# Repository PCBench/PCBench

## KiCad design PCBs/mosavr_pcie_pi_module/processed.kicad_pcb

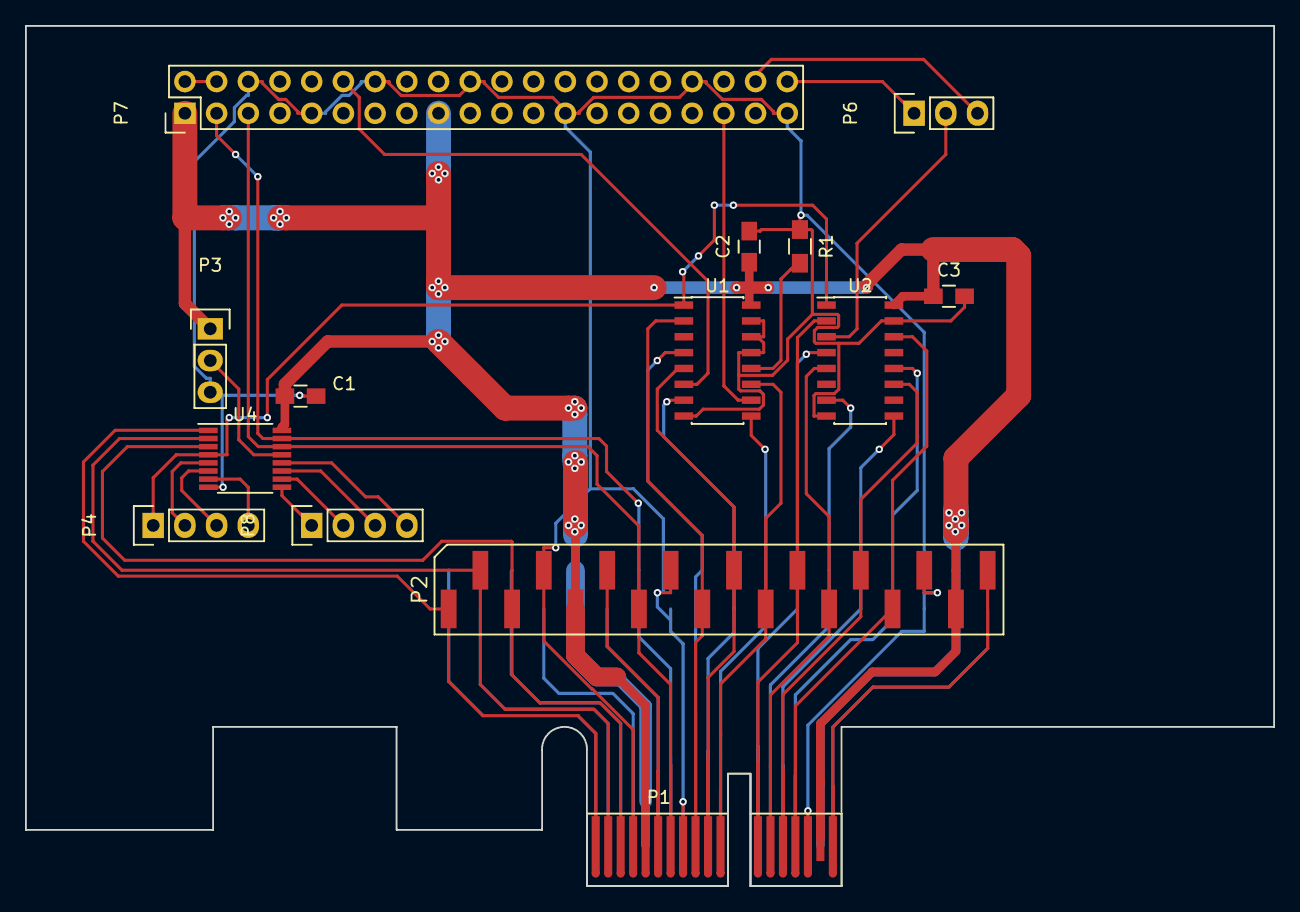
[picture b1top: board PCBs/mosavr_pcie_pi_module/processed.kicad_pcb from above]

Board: 2 copper layers, 100.0 x 68.9 mm, 15 parts (1 on the bottom side), 45 nets.

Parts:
C1, C2, C3: 0.1uF; C_0805_HandSoldering
P1: pcie_1x_edge; PCI-EXPRESS
P2, P5: CONN_01X18; smd_1x18_B
P3, P6: CONN_01X03; Pin_Header_Straight_1x03
P4, P8: CONN_01X04; Pin_Header_Straight_1x04
P7: CONN_02X20; Pin_Header_Straight_2x20
R1: 10k; R_0805_HandSoldering
U1, U2: 74HCT157; SOIC-16_3.9x9.9mm_Pitch1.27mm
U4: PCA9500; TSSOP-16_4.4x5mm_Pitch0.65mm

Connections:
+3V3: C1.1, C2.1, C3.1, P1.A5, P1.A17, P1.B5, P1.B17, P2.5, P2.17, P3.1, P5.5, P5.17, P7.1, P7.17, U1.16, U2.16, U4.16
+5V: P7.2, P7.4
/A0: P1.B1, P2.1, U4.1
/A1: P1.B2, P2.2, U4.2
/A2: P1.B3, P2.3, U4.3
/I2S0_in: P1.B12, P2.12, U2.2
/I2S0_mod: P6.2, U2.3
/I2S0_out: P1.A12, P5.12, U2.4
/I2S1_in: P1.B13, P2.13, U2.5
/I2S1_out: P1.A13, P5.13, U2.7
/I2S2_in: P1.B14, P2.14, U2.11
/I2S2_out: P1.A14, P5.14, U2.9
/I2S3_in: P1.B15, P2.15, U2.14
/I2S3_out: P1.A15, P5.15, U2.12
/LRclk_in: P1.B11, P2.11, U1.11
/LRclk_mod: P7.35, U1.10
/LRclk_out: P1.A11, P5.11, U1.9
/Mclk_in: P1.B9, P2.9, U1.2
/Mclk_out: P1.A9, P5.9, U1.4
/SCL: P1.B7, P2.7, P7.5, U4.14
/SDA: P1.A7, P5.7, P7.3, U4.15
/Sclk_in: P1.B10, P2.10, U1.5
/Sclk_mod: P7.12, U1.6
/Sclk_out: P1.A10, P5.10, U1.7
/pi_header/I2S_in_to_pi: P6.3, P7.38
/pi_header/I2S_out_from_pi: P6.1, P7.40
GND: C1.2, C2.2, C3.2, P1.A8, P1.A16, P1.B4, P1.B8, P1.B16, P2.4, P2.8, P2.16, P3.3, P5.8, P5.16, P7.6, P7.9, P7.14, P7.20, P7.25, P7.34, P7.39, R1.1, U1.8, U1.13, U1.14, U1.15, U2.8, U2.15, U4.8
unnamed: P1.A1, P5.1
unnamed: P1.A2, P5.2
unnamed: P1.A3, P5.3
unnamed: P1.A4, P5.4
unnamed: P1.A6, P5.6
unnamed: P1.A18, P5.18
unnamed: P1.B6, P2.6
unnamed: P1.B18, P2.18
unnamed: P3.2, U4.13
unnamed: P4.1, U1.1, U2.1, U4.4
unnamed: P4.2, U4.5
unnamed: P4.3, U4.6
unnamed: P4.4, U4.7
unnamed: P8.1, U4.9
unnamed: P8.2, U4.10
unnamed: P8.3, U4.11
unnamed: P8.4, U4.12
unnamed: R1.2, U1.12

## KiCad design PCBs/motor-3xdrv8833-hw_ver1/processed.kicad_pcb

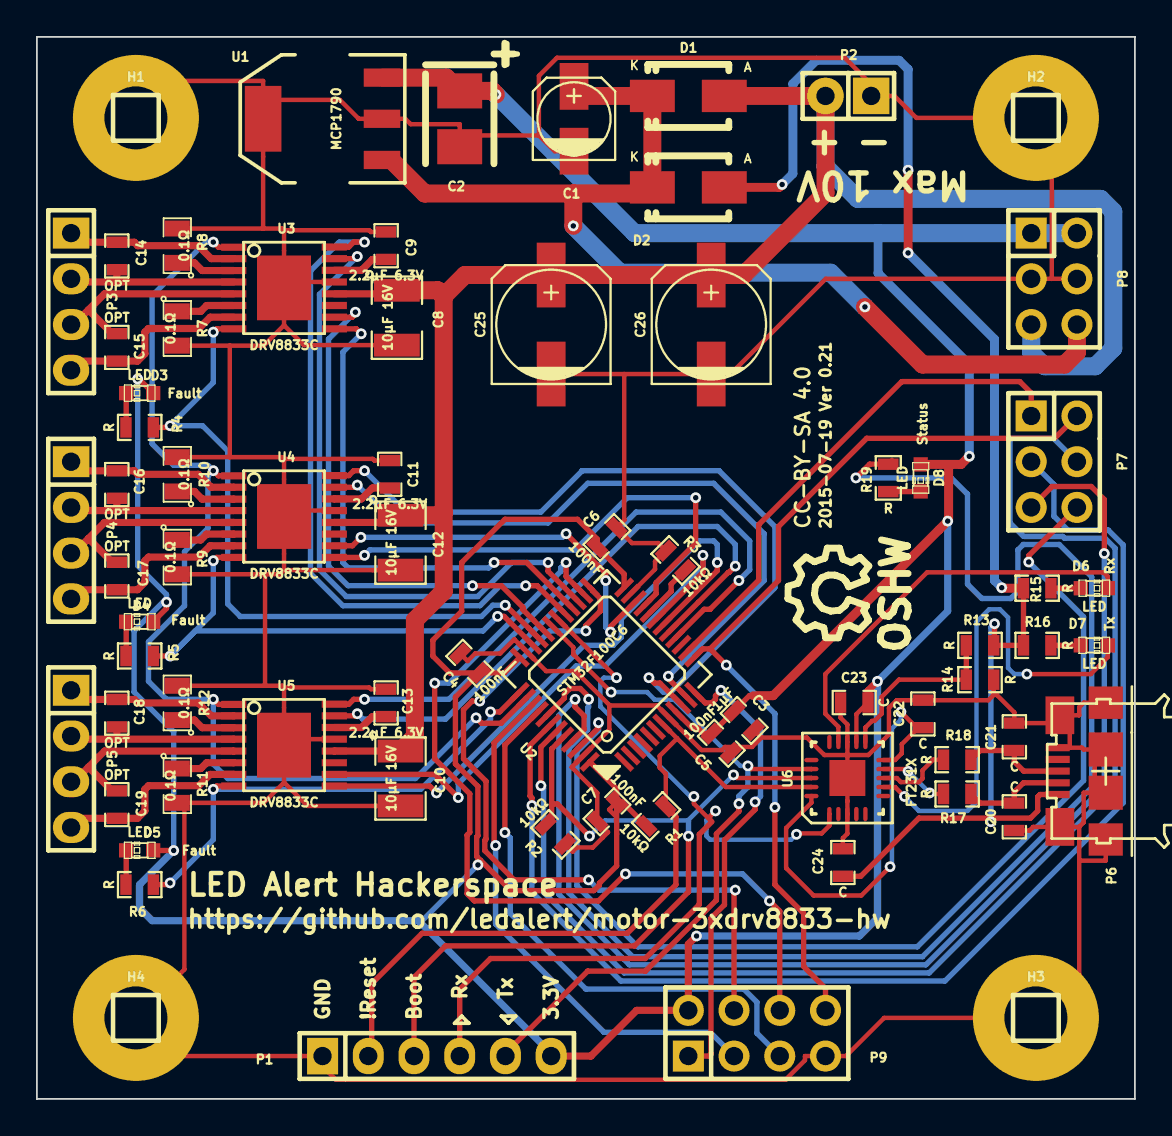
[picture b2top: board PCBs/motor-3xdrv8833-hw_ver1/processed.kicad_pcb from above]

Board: 2 copper layers, 61.0 x 59.0 mm, 73 parts (0 on the bottom side), 73 nets.

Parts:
C1: 1µF 35V; c_elec_4x5.3
C2: 1µF 6.3V; TantalC_SizeB_EIA-3528_Reflow
C3: 1µF; SMD-0603_c
C4, C5, C6, C7: 100nF; SMD-0603_c
C8, C10, C12: 10µF 16V; SMD-1210
C9, C11, C13: 2.2µF 6.3V; SMD-0603_c
C14, C15, C16, C17, C18, C19: OPT; SMD-0603_c
C20, C21, C22, C23, C24: C; SMD-0603_c
C25, C26: 220µF 16V; c_elec_6.3x7.7
D1, D2: DIODESCH; Diode-SMA_Standard
D3, D4, D5, D6, D7, D8: LED; LED-0603
H1, H2, H3, H4: CONN_1; Pin_Header_Straight_1x01
P1: CONN_6; Pin_Header_Straight_1x06
P2: CONN_2; Pin_Header_Straight_1x02
P3, P4, P5: CONN_4; Pin_Header_Straight_1x04
P6: USB_Micro_B; USB MICRO B
P7, P8: CONN_3X2; Pin_Header_Straight_2x03
P9: CONN_4X2; Pin_Header_Straight_2x04
R1, R2, R3: 10kΩ; SMD-0603_r
R4, R5, R6, R13, R14, R15, R16, R17, R18, R19: R; SMD-0603_r
R7, R8, R9, R10, R11, R12: 0.1Ω; SMD-0805
SYM: Symbol_OSHW-Logo_SilkScreen_07Jul2012; Symbol_OSHW-Logo_SilkScreen
U1: MCP1790; SOT-223
U2: STM32F100C6; lqfp-48
U3, U4, U5: DRV8833C; SSOP-16(EP)
U6: FT231X; QFN_20-1EP

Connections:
/BOOT1: R3.1, U2.20
/ESP8266 PTH Connector/CH_PD: P9.6, U2.26
/ESP8266 PTH Connector/GPIO0: P9.3, U2.39
/ESP8266 PTH Connector/GPIO2: P9.5, U2.40
/ESP8266 PTH Connector/RST: P9.4, U2.25
/ESP8266 PTH Connector/RXD: P9.1, U2.12
/ESP8266 PTH Connector/TXD: P7.2, P9.8, U2.13
/GPIO1: P7.1, U2.14
/GPIO5: P7.3, U2.42
/GPIO6: P7.4, U2.43
/GPIO7: P7.5, U2.45
/GPIO8: P7.6, U2.46
/PC Interface/DTR: P1.3, R2.1, U2.44, U6.18
/PC Interface/RTS: P1.2, R1.2, U2.7, U6.19
/PC Interface/RX: P1.4, U2.30, U6.1
/PC Interface/TX: P1.5, U2.31, U6.17
/PC Interface/VBUS: C24.1, D2.1, P6.1, R13.2, R15.2, R16.2
/STATUS_LED: R19.2, U2.41
/VDD_INT: C1.1, D1.2, D2.2, P8.6, U1.1
/drv8833_1/AIN1: U2.29, U3.16
/drv8833_1/AIN2: U2.27, U3.15
/drv8833_1/AOUT1: C14.2, P3.1, U3.2
/drv8833_1/AOUT2: C14.1, P3.2, U3.4
/drv8833_1/BIN1: U2.28, U3.9
/drv8833_1/BIN2: U2.32, U3.10
/drv8833_1/BOUT1: C15.2, P3.4, U3.7
/drv8833_1/BOUT2: C15.1, P3.3, U3.5
/drv8833_1/FAULT_OUT: R4.2, U2.33, U3.8
/drv8833_1/SLEEP_IN: U2.38, U3.1, U4.1, U5.1
/drv8833_2/AIN1: U2.10, U4.16
/drv8833_2/AIN2: U2.11, U4.15
/drv8833_2/AOUT1: C16.2, P4.1, U4.2
/drv8833_2/AOUT2: C16.1, P4.2, U4.4
/drv8833_2/BIN1: U2.21, U4.9
/drv8833_2/BIN2: U2.22, U4.10
/drv8833_2/BOUT1: C17.2, P4.4, U4.7
/drv8833_2/BOUT2: C17.1, P4.3, U4.5
/drv8833_2/FAULT_OUT: R5.2, U2.34, U4.8
/drv8833_3/AIN1: U2.16, U5.16
/drv8833_3/AIN2: U2.17, U5.15
/drv8833_3/AOUT1: C18.2, P5.1, U5.2
/drv8833_3/AOUT2: C18.1, P5.2, U5.4
/drv8833_3/BIN1: U2.18, U5.9
/drv8833_3/BIN2: U2.19, U5.10
/drv8833_3/BOUT1: C19.2, P5.4, U5.7
/drv8833_3/BOUT2: C19.1, P5.3, U5.5
/drv8833_3/FAULT_OUT: R6.2, U2.37, U5.8
GND: C1.2, C2.2, C3.2, C4.2, C5.2, C6.2, C7.2, C8.2, C9.2, C10.2, C11.2, C12.2, C13.2, C20.2, C21.2, C22.2, C23.2, C24.2, C25.2, C26.2, H1.1, H2.1, H3.1, H4.1, P1.1, P2.1, P6.5, P6.S, P8.3, P8.4, P9.7, R2.2, R3.2, R7.2, R8.2, R9.2, R10.2, R11.2, R12.2, R14.1, U1.2, U1.4, U2.8, U2.23, U2.35, U2.47, U3.13, U3.17, U4.13, U4.17, U5.13, U5.17, U6.3, U6.13, U6.21
unnamed: C9.1, U3.14
unnamed: C11.1, U4.14
unnamed: C13.1, U5.14
unnamed: C20.1, P6.2, R17.2
unnamed: C21.1, P6.3, R18.2
unnamed: C22.1, U6.10, U6.20
unnamed: D3.2, R4.1
unnamed: D4.2, R5.1
unnamed: D5.2, R6.1
unnamed: D6.1, R15.1
unnamed: D6.2, U6.14
unnamed: D7.1, R16.1
unnamed: D7.2, U6.7
unnamed: D8.2, R19.1
unnamed: R7.1, U3.6
unnamed: R8.1, U3.3
unnamed: R9.1, U4.6
unnamed: R10.1, U4.3
unnamed: R11.1, U5.6
unnamed: R12.1, U5.3
unnamed: R13.1, R14.2, U6.11
unnamed: R17.1, U6.9
unnamed: R18.1, U6.8
VCC: C2.1, C3.1, C4.1, C5.1, C6.1, C7.1, C23.1, D3.1, D4.1, D5.1, D8.1, P1.6, P8.1, P8.2, P9.2, R1.1, U1.3, U2.9, U2.24, U2.36, U2.48, U6.12
VDD: C8.1, C10.1, C12.1, C25.1, C26.1, D1.1, P2.2, P8.5, U3.12, U4.12, U5.12

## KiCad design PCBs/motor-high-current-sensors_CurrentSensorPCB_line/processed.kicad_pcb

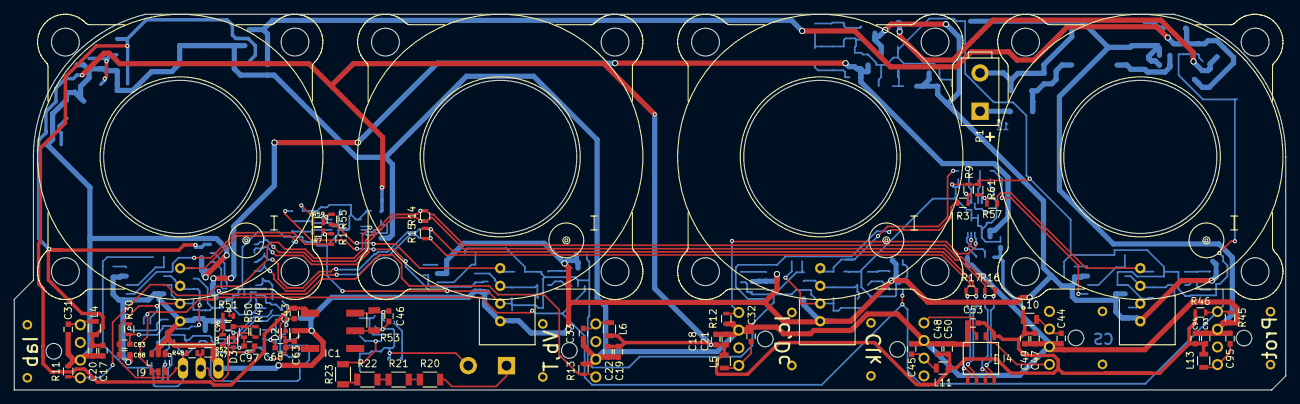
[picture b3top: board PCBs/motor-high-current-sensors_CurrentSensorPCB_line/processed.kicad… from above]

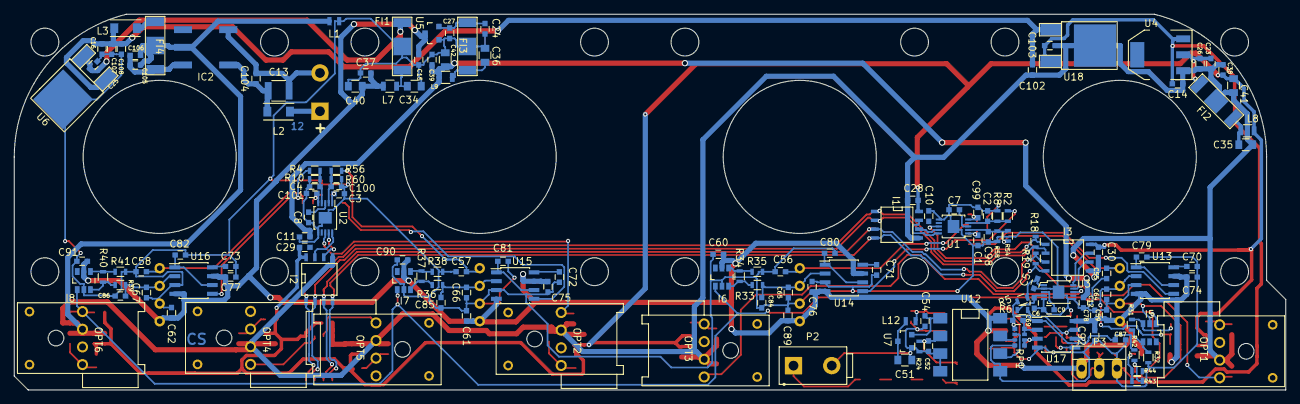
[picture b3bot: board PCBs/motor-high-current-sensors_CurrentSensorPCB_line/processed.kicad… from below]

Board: 2 copper layers, 182.8 x 54.0 mm, 222 parts (150 on the bottom side), 102 nets.

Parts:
C1, C2, C3, C4, C5, C6, C98, C99, C100, C101: 5.1n; C_0603
C7, C8, C9, C10, C11, C12, C20, C21, C22, C31, C32, C33, C44, C45, C47, C48, C94, C95: 10u; C_0603
C13: 22u, 16V; C_1210
C14, C15, C16, C17, C18, C19, C28, C29, C30, C43, C49, C50, C53, C74, C75, C76, C77, C79, C80, C81, C82, C88, C89, C90, C91, C92, C93, C102: 100n; C_0603
C23, C24, C25, C54, C103, C105, C107: 1u; C_0603
C26, C27, C46, C68, C69, C104, C106, C108: 1n; C_0603
C34, C35, C36: 10u, 6.3v; C_0805
C37, C38, C39, C52: 10n; C_0603
C40, C41, C42, C51: 4u7; C_0805
C55, C56, C57, C58, C59, C60, C61, C62, C63, C78, C83, C84, C85, C86, C87, C96, C97: 47n; C_0603
C64, C65, C66, C67: 4n7; C_0603
C70, C71, C72, C73: 27p; C_0603
D2, D3: 3.3V; SOD-523
FI1, FI2, FI3, FI4: NFE61P; EMI_Filter_murata
I1, I2, I3: DS90LV028A; SOIC-8-N
I4: DS90LV027A; SOIC-8-N
I5, I6, I7, I8, I9: ADCMP671; TSOT-6-MK06A
IC1, IC2: Murata_MTU1; MTU1_Murata_DCDC
L1: INDUCTOR_SMALL; Neosid_Inductor_SM0603CG
L2, L3: 10uH; Neosid_Inductor_SM1206
L4, L5, L6, L10, L11, L13: 1uH; R_0805
L7, L8, L9: ?; R_0805
L12: 10uH; Neosid_Inductor_SM0603CG
OPT1, OPT2, OPT3, OPT6: AFBR-1634Z; HFBR-xx3xZ
OPT4, OPT5: AFBR-26x; HFBR-xx3xZ
P1, P2: CONN_01X02; Connector_Header_2Way_39-29-3026
P3: CONN_01X03; PINHEAD1-3
R1, R2, R3, R4, R54, R55, R56, R57: 3.6k; R_0603
R5, R6: 51; R_0603
R7, R8, R9, R10, R58, R59, R60, R61: 6.8k; R_0603
R11, R12, R13, R46: 4k7; R_0603
R14, R15, R16, R17, R18, R19: 330; R_0603
R20, R21, R22, R23: 100k; R_1206
R24: 158; R_0603
R30, R33, R36, R39: 1k6; R_0603
R31, R34, R37, R40: 910; R_0603
R32, R35, R38, R41: 270; R_0603
R42, R43, R44, R45, R47, R48, R49, R50, R51: DNP; R_0603
R52: 0R; R_0603
R53: 270; R_1206
RP1: R_PACK4; ACAS0612
U1, U2: LTC1407-1; MSOP-10-1EP_3x3mm_Pitch0.5mm
U3: LTC1407; MSOP-10-1EP_3x3mm_Pitch0.5mm
U4: LD1117S33TR; SOT-223
U5: MCP1700T-330; SOT-23
U6, U18: MC78M05CDT; TO-252-2Lead
U7: MCP1700T-500; SOT-23
U8, U9, U10: HTFS800; HTFS-Series_LEM-HallEffektCurrentTransducer
U11: HTFS400; HTFS-Series_LEM-HallEffektCurrentTransducer
U12: ACPL-C870; DIP-8_SMD
U13, U14, U15, U16: MAX7480; SOIC-8_3.9x4.9mm_Pitch1.27mm
U17: OPA350; SOIC-8_3.9x4.9mm_Pitch1.27mm

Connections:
+3.3VADC: C11.2, C12.2, C39.1, C42.1, L9.2
+3V3: C17.2, C18.2, C19.2, C20.2, C21.2, C22.2, C28.2, C29.2, C30.2, C38.1, C41.1, C47.2, C48.2, C49.2, C50.2, C53.2, C93.2, C94.2, I1.8, I2.8, I3.8, I4.1, L4.1, L5.1, L6.1, L8.2, L10.1, L11.1, L13.1, R46.1
+5V: C14.1, C43.1, C103.1, IC1.1, U4.3, U18.3
+5VA: C15.1, C37.1, C40.1, C59.2, C60.2, C61.2, C62.2, C63.2, C74.1, C75.1, C76.1, C77.1, C78.1, C88.2, C89.2, C90.2, C91.2, C92.2, I6.5, I7.5, I8.5, I9.5, L7.2, P3.1, R47.2, U5.3, U8.1, U9.1, U10.1, U11.1, U12.8, U13.4, U13.7, U14.4, U14.7, U15.4, U15.7, U16.4, U16.7, U17.8
+9V: C16.1, C102.1, C107.1, C108.1, L3.2, U6.1, U18.1
/ADC_Ck+: I1.3, I2.3, I3.3, I4.6, R15.2, R17.2, R19.2
/ADC_Ck-: I1.4, I2.4, I3.4, I4.5, R15.1, R17.1, R19.1
/ADC_Smp+: I1.2, I2.2, I3.2, I4.7, R14.1, R16.1, R18.1
/ADC_Smp-: I1.1, I2.1, I3.1, I4.8, R14.2, R16.2, R18.2
/I_U: R1.2, U13.5
/I_V: R2.2, U14.5
/I_W: R3.2, U15.5
/I_bus: R4.2, U16.5
/I_bus_sense: C67.1, C86.1, R39.2, U11.3, U16.2
/I_u_sense: C64.1, C83.1, R30.2, U8.3, U13.2
/I_v_sense: C65.1, C84.1, R33.2, U9.3, U14.2
/I_w_sense: C66.1, C85.1, R36.2, U10.3, U15.2
/Over_IV_prot: I5.1, I6.1, I7.1, I8.1, I9.1, OPT6.4, R45.2, R46.2
/T_coolant: D3.1, R6.2, R52.1, U17.7
/V_bus: C69.2, C87.1, D2.1, R5.2, R42.2, RP1.4, U17.1
/V_ref_U: C55.1, R54.1, U8.4
/V_ref_V: C56.1, R55.2, U9.4
/V_ref_W: C57.1, R56.1, U10.4
/V_ref_bus: C58.1, R57.2, U11.4
AGND: C1.1, C2.1, C3.1, C4.1, C5.1, C6.1, C7.2, C8.2, C9.2, C10.1, C11.1, C12.1, C15.2, C16.2, C24.2, C25.2, C27.2, C34.2, C36.2, C37.2, C39.2, C40.2, C42.2, C43.2, C55.2, C56.2, C57.2, C58.2, C59.1, C60.1, C61.1, C62.1, C63.1, C64.2, C65.2, C66.2, C67.2, C68.2, C70.2, C71.2, C72.2, C73.2, C74.2, C75.2, C76.2, C77.2, C78.2, C79.2, C80.2, C81.2, C82.2, C83.2, C84.2, C85.2, C86.2, C87.2, C88.1, C89.1, C90.1, C91.1, C92.1, C97.2, C98.2, C99.2, C100.2, C101.2, C107.2, C108.2, D2.2, D3.2, FI1.2, FI3.2, I5.2, I6.2, I7.2, I8.2, I9.2, IC1.3, L1.2, P3.3, R7.1, R8.1, R9.1, R10.1, R32.1, R35.1, R38.1, R41.1, R44.1, R48.1, R51.1, R58.1, R59.1, R60.1, R61.1, RP1.1, U1.6, U1.11, U2.6, U2.11, U3.2, U3.5, U3.6, U3.11, U5.1, U6.2, U8.2, U9.2, U10.2, U11.2, U12.5, U13.3, U14.3, U15.3, U16.3, U17.4
DGND: C14.2, C17.1, C18.1, C19.1, C20.1, C21.1, C22.1, C23.2, C26.2, C28.1, C30.1, C31.1, C32.1, C33.1, C35.2, C38.2, C41.2, C44.1, C45.1, C47.1, C48.1, C49.1, C50.1, C53.1, C93.1, C94.1, C95.1, C102.2, C103.2, C105.2, C106.2, FI2.2, FI4.2, I1.5, I2.5, I3.5, I4.4, IC2.5, L1.1, OPT1.3, OPT2.3, OPT3.3, OPT4.2, OPT5.2, OPT6.3, R11.1, R12.1, R13.1, R45.1, U4.1, U18.2
unnamed: C1.2, R1.1, R7.2, U1.1
unnamed: C2.2, R2.1, R8.2, U1.4
unnamed: C3.2, R3.1, R9.2, U2.1
unnamed: C4.2, R4.1, R10.2, U2.4
unnamed: C5.2, R5.1, U3.1
unnamed: C6.2, R6.1, U3.4
unnamed: C7.1, U1.3
unnamed: C8.1, U2.3
unnamed: C9.1, U3.3
unnamed: C23.1, C26.1, FI2.1, U4.2
unnamed: C24.1, C27.1, FI3.1, U5.2
unnamed: C25.1, FI1.1, U6.3
unnamed: C31.2, L4.2, OPT1.1
unnamed: C32.2, L5.2, OPT2.1
unnamed: C33.2, L6.2, OPT3.1
unnamed: C34.1, FI1.3, L7.1
unnamed: C35.1, FI2.3, L8.1
unnamed: C36.1, FI3.3, L9.1
unnamed: C44.2, L10.2, OPT4.3
unnamed: C45.2, L11.2, OPT5.3
unnamed: C46.1, C51.2, C52.2, C54.2, IC1.5, P2.2, R24.2, R53.1, U7.1, U12.3, U12.4
unnamed: C46.2, IC1.6, L12.1, R53.2
unnamed: C51.1, L12.2, U7.3
unnamed: C52.1, R23.1, R24.1, U12.2
unnamed: C54.1, U7.2, U12.1
unnamed: C68.1, RP1.7, RP1.8, U17.3
unnamed: C69.1, RP1.5, RP1.6, U17.2
unnamed: C70.1, U13.8
unnamed: C71.1, U14.8
unnamed: C72.1, U15.8
unnamed: C73.1, U16.8
unnamed: C79.1, U13.1, U13.6
unnamed: C80.1, U14.1, U14.6
unnamed: C81.1, U15.1, U15.6
unnamed: C82.1, U16.1, U16.6
unnamed: C95.2, L13.2, OPT6.1
unnamed: C96.1, R51.2, R52.2, U17.6
unnamed: C96.2, R49.1, R50.2
unnamed: C97.1, R50.1, U17.5
unnamed: C98.1, R54.2, R58.2, U1.2
unnamed: C99.1, R55.1, R59.2, U1.5
unnamed: C100.1, R56.2, R60.2, U2.2
unnamed: C101.1, R57.1, R61.2, U2.5
unnamed: C13.2, C104.1, IC2.3, P1.2
unnamed: C13.1, C104.2, IC2.1, L2.2
unnamed: C105.1, C106.1, FI4.1, IC2.6
unnamed: FI4.3, L3.1
unnamed: I1.6, U1.9
unnamed: I1.7, U1.10
unnamed: I2.6, U2.9
unnamed: I2.7, U2.10
unnamed: I3.6, U3.9
unnamed: I3.7, U3.10
unnamed: I4.2, OPT4.1
unnamed: I4.3, OPT5.1
unnamed: I5.3, R30.1, R31.2
unnamed: I5.4, R31.1, R32.2
unnamed: I6.3, R33.1, R34.2
unnamed: I6.4, R34.1, R35.2
unnamed: I7.3, R36.1, R37.2
unnamed: I7.4, R37.1, R38.2
unnamed: I8.3, R39.1, R40.2
unnamed: I8.4, R40.1, R41.2
unnamed: I9.3, R42.1, R43.2
unnamed: I9.4, R43.1, R44.2
unnamed: L2.1, P1.1
unnamed: OPT1.4, R11.2, U1.8
unnamed: OPT2.4, R12.2, U2.8
unnamed: OPT3.4, R13.2, U3.8
unnamed: P2.1, R20.2
unnamed: P3.2, R47.1, R48.2, R49.2
unnamed: R20.1, R21.2
unnamed: R21.1, R22.2
unnamed: R22.1, R23.2
unnamed: RP1.2, U12.7
unnamed: RP1.3, U12.6

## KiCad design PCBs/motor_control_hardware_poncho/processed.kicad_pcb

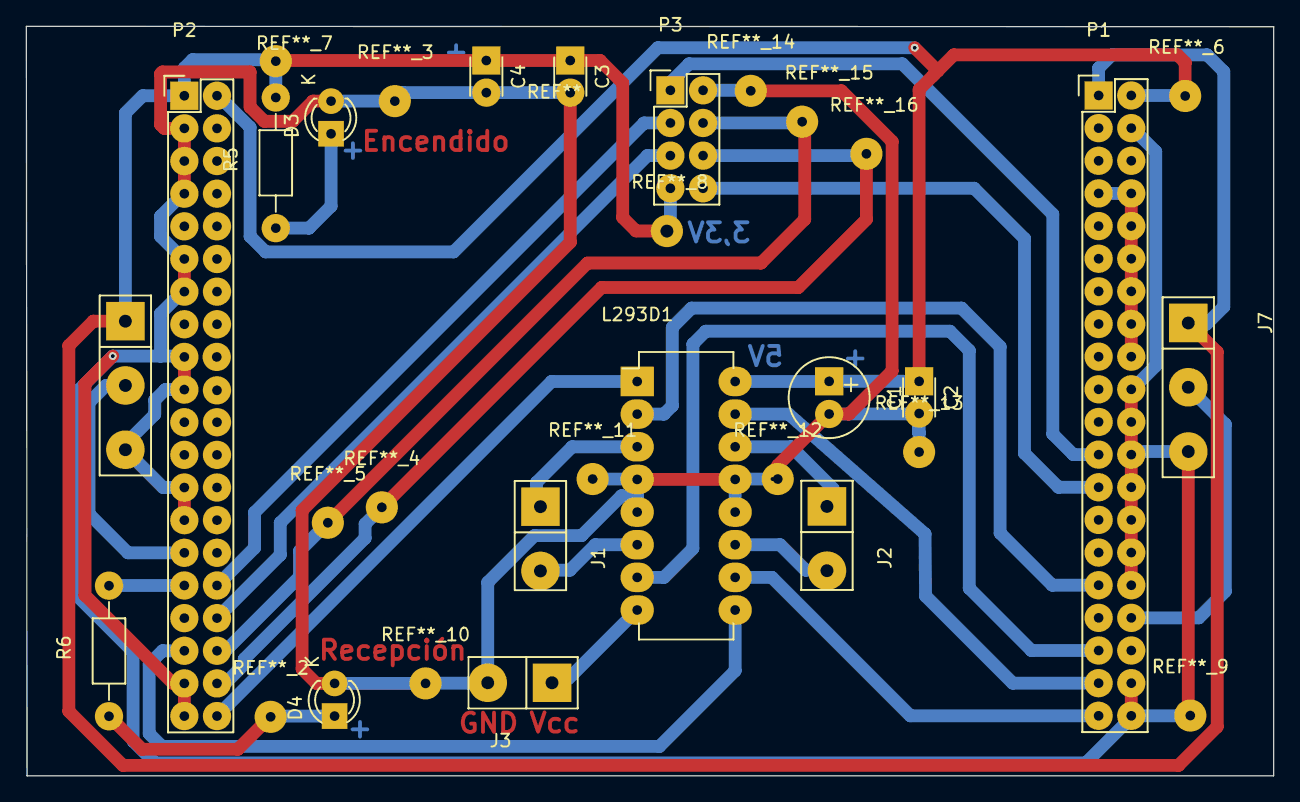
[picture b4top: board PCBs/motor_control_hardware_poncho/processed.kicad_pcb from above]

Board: 2 copper layers, 97.0 x 58.3 mm, 17 parts (0 on the bottom side), 26 nets.

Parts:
C1: CP; Elko_vert_11.2x6.3mm_RM2.5
C2, C3, C4: C; C_Disc_D3_P2.5
D3, D4: LED; LED-3MM
J1, J2, J3: TB_1X2; bornera1x2
J6, J7: TB_1X3; bornera1x3
L293D1: L293D; DIP-16_W7.62mm_LongPads
P1, P2: CONN_20X2; Pin_Header_Straight_2x20
P3: ESP8266; Pin_Header_Straight_2x04
R5, R6: R; Resistor_Horizontal_RM10mm

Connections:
+3V3: C3.1, C4.1, J6.1, J7.1, P1.1, P2.1, P3.4, R5.2
+5V: C1.1, C2.1, L293D1.16, P1.2, P2.2
/ENG0_OUT0: J1.1, L293D1.3
/ENG0_OUT1: J1.2, L293D1.6
/ENG1_OUT0: J2.1, L293D1.14
/ENG1_OUT1: J2.2, L293D1.11
/GPIO0: J6.2, P2.29
/GPIO1: P2.32, P3.2
/GPIO2: P2.31, R6.2
/GPIO3: P2.34, P3.3
/GPIO5: P2.36, P3.7
/GPIO6: L293D1.9, P2.35
/GPIO7: P2.38, P3.6
/GPIO8: L293D1.1, P2.40
/MOTOR_VCC: J3.1, L293D1.8
/RS232_RXD: P1.23, P3.1
/RS232_TXD: P1.25, P3.5
/TEC_COL0: L293D1.10, P1.39
/TEC_COL1: L293D1.2, P1.31
/TEC_COL2: J7.2, P1.34
/TEC_F2: L293D1.15, P1.37
/TEC_F3: L293D1.7, P1.35
GND: C1.2, C2.2, C3.2, C4.2, D3.1, D4.1, J3.2, J6.3, J7.3, L293D1.4, L293D1.5, L293D1.12, L293D1.13, P1.4, P1.20, P1.22, P1.24, P1.26, P1.28, P1.30, P1.32, P1.38, P1.40, P2.3, P2.5, P2.7, P2.11, P2.13, P2.17, P2.19, P2.25, P2.27, P2.37, P2.39, P3.8
GNDA: P1.7, P1.8, P1.10, P1.12, P1.14, P1.16, P1.18
unnamed: D3.2, R5.1
unnamed: D4.2, R6.1

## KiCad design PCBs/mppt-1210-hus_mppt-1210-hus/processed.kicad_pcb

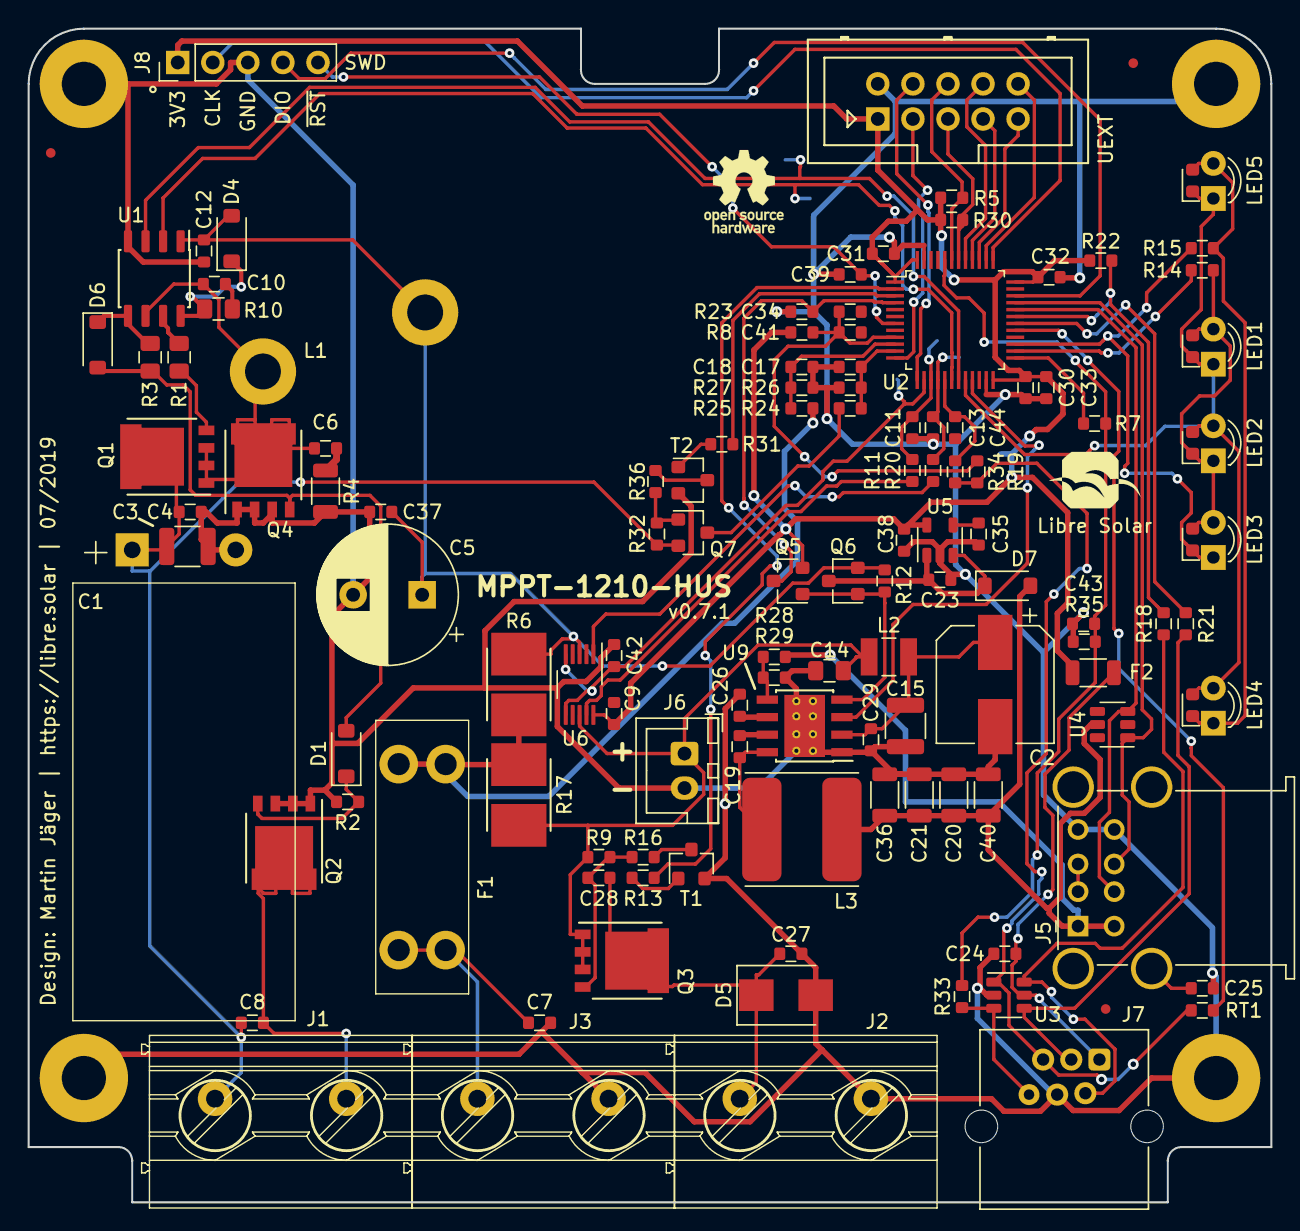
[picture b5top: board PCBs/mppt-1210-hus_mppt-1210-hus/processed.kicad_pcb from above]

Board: 2 copper layers, 90.0 x 85.0 mm, 132 parts (0 on the bottom side), 79 nets.

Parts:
C1: 1200u; CP_Radial_L31.5mm_D16.0mm_P7.50mm_horizontal
C2: 150u; CP_Elec_8x6.2
C3: 4.7u; C_1210_3225
C4, C7, C8, C17, C18, C27, C28, C37, C41, C44: 10n; C_0603_1608
C5: 820u; CP_Radial_D10.0mm_P5.00mm
C6, C11, C13: 1n; C_0603_1608
C9, C10, C19, C24, C25, C26, C30, C31, C32, C39, C42, C43: 100n; C_0603_1608
C12, C23, C33, C34, C38: 2.2u; C_0603_1608
C14: 1u; C_0805_2012
C15: 10u; C_1210_3225
C20, C21, C36, C40: 22u; C_1206_3216
C29: 220n; C_0603_1608
C35: 100p; C_0603_1608
D1, D4, D7: 1N4148; D_SOD-123
D5: SMBJ24A; D_SMB
D6: SS14FL; D_SOD-123
F1: 25A; KEYSTONE-FUSE-3557-2
F2: 50mA; R_1206_3216
J1, J2, J3: MKDS_5-2_952; Phoenix_Contact_MKDS_5-2-952
J4: UEXT; Box_Header_2x05x2.54mm_Straight
J5: USB_A_stacked; USB_A_Wuerth_61400826021_Horizontal_Stacked
J6: PWR_12V; JST_XH_B02B-XH-A_1x02_P2.50mm_Vertical
J7: 6P6C; RJ25_6P6C_TabUp
J8: ST_Nucleo_SWD; PinHeader_1x05_P2.54mm_Vertical
L1: 47uH; L-FERYSTER-DTMSS-27_47uH
L2: 2.2uH; L_1210_3225Metric
L3: 10uH; Bourns_SRN8040TA
LED1, LED2, LED3: yellow; LED_0603_D3.0mm
LED4, LED5: green; LED_0603_D3.0mm
LOGO1: LIBRE_SOLAR; LIBRESOLAR_LOGO
LOGO2: OPEN_HARDWARE; OSHW-Logo_5.7x6mm_SilkScreen
MK1, MK2, MK3, MK4: Mounting_Hole; MountingHole_3.2mm_M3_Pad
Q1, Q2, Q4: PSMN5R2-60YLX; 5X6_MOSFET
Q3: BSC084P03NS3; 5X6_MOSFET
Q5, Q6, Q7: BSS83P; SOT-23
R1, R3, R10: 4.7; R_0805_2012
R2: 1M; R_0603_1608
R4: 2.2; R_1206_3216
R5, R7, R13, R30, R33, R34: 2.2k; R_0603_1608
R6, R17: 3m; R_Bourns_CRE2512
R8: 100; R_0603_1608
R9, R16, R19, R31: 10k; R_0603_1608
R11, R14, R15, R18, R20, R21: 470; R_0603_1608
R12, R22, R23, R24, R25, R28, R35, R36: 100k; R_0603_1608
R26, R27: 5.6k; R_0603_1608
R29, R32: 24.9k; R_0603_1608
RT1: 10k NTC; R_0603_1608
T1, T2: MMBT3904; SOT-23
TP1, TP2, TP3, TP4, TP5, TP6, TP7, TP9: Test_Point_Probe; TestPoint_Pad_D1.0mm
U1: LM5109BMA; SOIC-8_3.9x4.9mm_Pitch1.27mm
U2: STM32L072CZT6; LQFP-48_7x7mm_P0.5mm
U3, U4: D1213A-04SO; SOT-23-6
U5: AP2210-3.3; SOT-23-5
U6: INA2181; VSSOP-10_3.0x3.0mm_P0.5mm
U9: LMR33630; TI_SO-PowerPAD-8_ThermalVias

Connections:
5V_PG: Q5.3, R23.2, U2.4
+3V3: C9.1, C30.1, C31.1, C32.1, C33.1, C38.1, F2.2, J4.1, J8.1, Q5.2, R5.2, R8.1, R22.1, R30.2, TP9.1, U2.1, U2.24, U2.36, U2.48, U5.5, U6.10
+5V: C20.1, C21.1, C36.1, C40.1, D7.2, J5.1, J5.5, L3.2, R28.1, TP7.1, U4.5
+12V: F1.1, R6.2, R17.1, R25.1, TP1.1
/DCDC power stage/BAT+: C7.1, F1.2, J3.1
/DCDC power stage/HS_DRV: R1.2, U1.7
/DCDC power stage/LS_DRV: D6.1, R3.2, U1.5
/DCDC power stage/SOLAR+: C1.1, C3.1, C4.1, C8.1, J1.1, Q1.D, Q7.2, R32.1
/DCDC power stage/SOLAR-: C8.2, J1.2, Q2.D
/DCDC power stage/SW_NODE: C6.1, C10.2, L1.1, Q1.S, Q4.D, U1.6
/MCU/BOOT0: C43.1, R7.2, R33.2, R35.2, U2.44
/MCU/BUTTON: R7.1, U2.25
/MCU/I2C1_SCL: J4.5, R30.1, U2.42
/MCU/I2C1_SDA: J4.6, R5.1, U2.43
/MCU/LED_A: R14.1, U2.26
/MCU/LED_B: LED3.1, R15.1, U2.27
/MCU/LED_C: LED1.1, LED2.2, LED4.2, LED5.1, U2.20
/MCU/SPI1_MISO: J4.7, U2.40
/MCU/SPI1_MOSI: J4.8, U2.41
/MCU/SPI1_SCK: J4.9, U2.39
/MCU/SSEL: J4.10, U2.38
/MCU/SWCLK: J8.2, U2.37
/MCU/SWDIO: J8.4, U2.34
/MCU/TEMP_EXT: J7.5, R19.2, R34.1, RT1.1, U3.1
/MCU/TEMP_INT_PD: RT1.2, U2.29
/MCU/USART1_RX: R18.2, R22.2, U2.31
/MCU/USART1_TX: R21.2, U2.30
/MCU/USART2_RX: J4.4, U2.13
/MCU/USART2_TX: J4.3, U2.12
/MCU/~RESET: C39.1, J8.5, U2.7
DAC: C42.1, TP6.1, U2.14, U6.5, U6.6
DCDC_OUT: C5.1, C12.1, C37.1, D4.2, L1.2, Q6.2, R6.1, R12.2, U1.1, U6.3
GND: C1.2, C2.2, C3.2, C4.2, C5.2, C7.2, C11.2, C12.2, C13.2, C14.2, C15.2, C17.2, C18.2, C20.2, C21.2, C23.2, C24.2, C25.2, C26.2, C27.2, C29.2, C30.2, C31.2, C32.2, C33.2, C35.2, C36.2, C37.2, C38.2, C39.2, C40.2, C42.2, C43.2, D5.2, J2.2, J3.2, J4.2, J5.4, J5.8, J6.2, J7.4, J8.3, MK1.1, MK2.1, MK3.1, MK4.1, Q2.S, Q4.S, R2.1, R4.1, R23.1, R26.2, R27.2, R29.2, R35.1, T1.2, T2.2, U1.4, U2.23, U2.47, U3.2, U5.2, U9.1, U9.9
I_DCDC: C13.1, R20.2, TP4.1, U2.16
I_LOAD: C11.1, R11.2, TP5.1, U2.15
LOAD+: C27.1, C28.1, D5.1, J2.1, Q3.D
LOAD_EN: R13.2, U2.2
LOAD_S: C14.1, J6.1, L2.1, Q3.S, R9.2, R17.2, U6.8
unnamed: C6.2, R4.2
unnamed: C10.1, R10.1
unnamed: C2.1, C15.1, C29.1, L2.2, U9.2
unnamed: C19.1, U9.7
unnamed: C19.2, L3.1, U9.8
unnamed: C23.1, D7.1, Q6.3, U5.1, U5.3
unnamed: C24.1, F2.1, J7.1, U3.5
unnamed: C25.1, J5.9
unnamed: C26.1, U9.6
unnamed: C28.2, Q3.G, R9.1, R16.2
unnamed: C35.1, U5.4
unnamed: D1.1, Q2.G, R2.2
unnamed: D1.2, D6.2, Q4.G, R3.1
unnamed: D4.1, R10.2, U1.8
unnamed: J5.2, J5.3
unnamed: J7.2, R18.1, U3.6
unnamed: J7.3, R21.1, U3.4
unnamed: J7.6, R33.1, U3.3
unnamed: LED1.2, LED2.1, LED3.2, R14.2
unnamed: LED4.1, LED5.2, R15.2
unnamed: Q1.G, R1.1
unnamed: Q5.1, Q6.1, R12.1, U9.4
unnamed: Q7.1, R32.2, R36.2
unnamed: Q7.3, R24.1
unnamed: R11.1, U6.9
unnamed: R13.1, T1.1
unnamed: R16.1, T1.3
unnamed: R20.1, U6.1
unnamed: R28.2, R29.1, U9.5
unnamed: R31.1, T2.1
unnamed: R36.1, T2.3
PWM_HS: TP2.1, U1.2, U2.18
PWM_LS: TP3.1, U1.3, U2.19
T_BAT: C44.1, R34.2, U2.17
USB_DM: J5.6, U2.32, U4.3
USB_DP: J5.7, U2.33, U4.1
USB_PWR_EN: U2.21, U9.3
VDDA: C34.1, C41.1, R8.2, R19.1, U2.9
V_BAT: C18.1, R25.2, R27.1, U2.10
V_SOLAR: C17.1, R24.2, R26.1, U2.11
V_SOLAR_EN: R31.2, U2.3

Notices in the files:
PCBs/motor-3xdrv8833-hw_ver1/processed.kicad_pcb:
CC-BY-SA 4.0
PCBs/mppt-1210-hus_mppt-1210-hus/processed.kicad_pcb:
Licensed under CERN-OHL-W version 2
